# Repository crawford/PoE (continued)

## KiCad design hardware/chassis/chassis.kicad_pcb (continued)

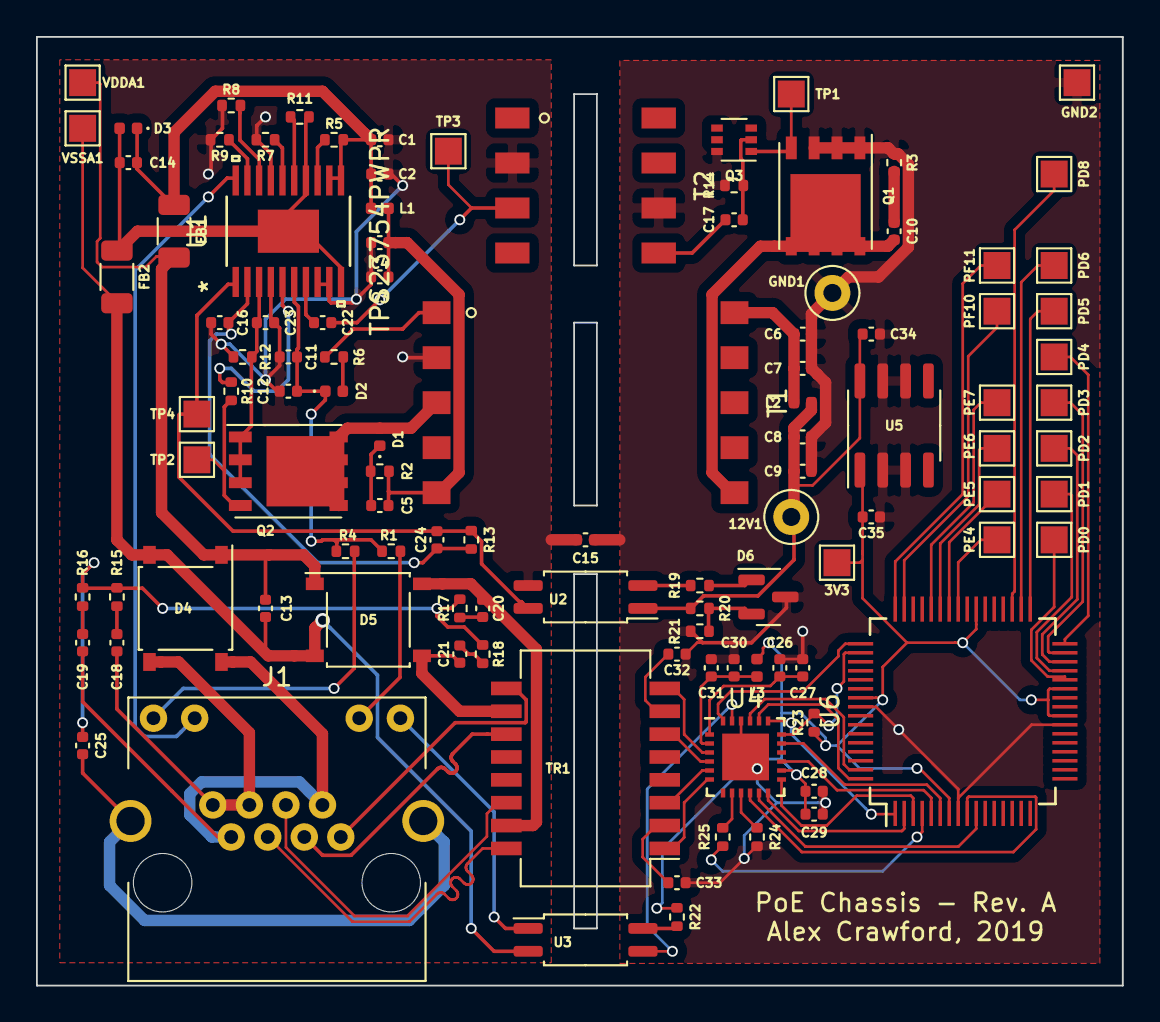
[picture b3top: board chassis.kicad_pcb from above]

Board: 2 copper layers, 60.3 x 52.7 mm, 108 parts (0 on the bottom side), 90 nets.

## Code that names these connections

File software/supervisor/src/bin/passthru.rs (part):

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use led::mono::{self, CommonAnodeLED};
use poe::fault;

type IdentifyLed = CommonAnodeLED<pins::PE4<Output>>;
type NetworkLed = CommonAnodeLED<pins::PE5<Output>>;

#[rtic::app(
    dispatchers = [ CAN0, CAN1, LCD ],
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        gpio_clk.enable();

        // TODO: Move into efm32gg-hal.
        // Configure PE13 as an input with pull-up, and enable interrupts on the falling edge. This
        // is connected to INTRP on the PHY.
        gpio.pe_modeh.modify(|_, w| w.mode13().input());
        gpio.extipselh.modify(|_, w| w.extipsel13().porte());
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        gpio.ien.write(|w| unsafe { w.ext().bits(1 << 13) });

        let gpio = gpio.split(gpio_clk);
        let _swo = gpio.pf2.as_output();

        let mut led_identify = IdentifyLed::new(CommonAnodeLED::new(gpio.pe4.as_opendrain()));
        let mut led_network = NetworkLed::new(CommonAnodeLED::new(gpio.pe5.as_opendrain()));

        led_identify.enable(false);

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            cx.device.ETH,
            &mut delay,
            efm32gg::Pins {
                rmii_rxd0: &mut gpio.pa2.as_input(),
                rmii_refclk: &mut gpio.pa3.as_output(),
                rmii_crsdv: &mut gpio.pa4.as_input(),
                rmii_rxer: &mut gpio.pa5.as_input(),
                rmii_mdio: &mut gpio.pb3.as_output(),
                rmii_mdc: &mut gpio.pb4.as_output(),
                rmii_txd0: &mut gpio.pe15.as_output(),
                rmii_txd1: &mut gpio.pe14.as_output(),
                rmii_txen: &mut gpio.pa0.as_output(),
                rmii_rxd1: &mut gpio.pa1.as_input(),
                phy_reset: &mut gpio.pe11.as_output(),
            },
            KSZ8091::new,
        )
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    let periph = unsafe { efm32gg11b820::Peripherals::steal() };
    let gpio = periph.GPIO.split(periph.CMU.constrain().split().gpio);

    let id = CommonAnodeLED::new(gpio.pe4.as_opendrain());
    let net = CommonAnodeLED::new(gpio.pe5.as_opendrain());

    (id, net)
}
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
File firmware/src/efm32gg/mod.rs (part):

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        // Hold the PHY module in reset
        pins.phy_reset.set_low().ignore();

        // Enable the PHY's reference clock on PA3 (CMU_CLK2 #1)
        cmu.routeloc0.modify(|_, reg| reg.clkout2loc().loc1());
        cmu.routepen.modify(|_, reg| reg.clkout2pen().set_bit());

        // Enable the MDC on PB4 (ETH_MDC #0) and MDIO on PB3 (ETH_MDIO #0)
        eth.routeloc1.write(|reg| {
            reg.rmiiloc().loc0();
            reg.mdioloc().loc0();
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
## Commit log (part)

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2018-03-02 firmware/cargo: update parameters for dev builds
    Development builds will be a bit closer to release builds.
2018-03-02 firmware: initial commit
    This adds an initial LED demo for the EFM32GG11-SLSTK3701A development
    beard.
2018-05-10 cargo: bump efm32gg11b820 to v0.3.0
    This is needed because the SVD was incorrect and didn't allow IFRC to be
    read.
2018-05-31 firmware/ethernet: add initial send/receive logic
    This initial implementation is able to send and receive packets, but
    it's still a little fragile.
2018-05-31 firmware/build: bump rust
    This resuilts in much smaller binaries (12.5% reduction).
2018-07-03 firmware/*: break EFM32GG into a MAC and PHY
    This defines a basic PHY interface so that alternate PHYs may eventually
    be used with the EFM32GG MAC. The KSZ8091 starts to implement this PHY
    interface. The EFM32GG MACPHY also no longer hardcodes the address of
    the PHY. It is dynamically discovered at runtime, further allowing
    alternate PHYs to be used in the future.
2018-07-07 firmware/build: bump rust
    There isn't really any reason for this other than to keep up-to-date.
2018-07-29 firmware/*: apply clippy recommendations
    This also results in smaller code!
2019-01-06 firmware/*: cargo fmt
    rustfmt 1.0.0-stable (4a4e508 2018-11-29)
2019-05-22 firmware/log: adjust logging levels
2019-09-16 hardware/*: remove netlist
    This file is no longer explicitly needed in KiCAD 5.
2019-09-16 hardware/*: various fixes based on review
2019-10-12 firmware/*: fix cortex-m deprecation warning
    cortex-m deprecated NVIC::enable in 0.6.1:
    warning: use of deprecated item 'cortex_m::peripheral::nvic::<impl
    cortex_m::peripheral::NVIC>::enable': Use `NVIC::unmask`
2019-12-08 firmware/main: log panic messages through ITM
    This will no longer light up both LEDs yellow, but instead send the panic message through the ITM.
2020-06-04 stash
2020-12-25 firmware/efm32gg: fix reuse of transmit buffer
    The ethernet module only sets the ownership bit of the first descriptor
    in a frame; not all of the descriptors. I guess I hadn't noticed because
    I've only been transmitting small payloads.
2021-07-05 cargo: update smoltcp
    Updating managed v0.7.2 -> v0.8.0
    Removing smoltcp v0.6.0
    Adding smoltcp v0.8.0 (https://github.com/smoltcp-rs/smoltcp#1134eb28)
2021-07-06 firmware/*: add some more logging
2021-07-11 main: clean up panic and fault handlers
2021-07-11 efm32gg: use slices to create buffer descriptors
    I dunno, this just seems more correct.
2021-07-11 efm32gg: clean up the IRQ
    This uses the LED resources instead of stealing them.
2021-07-11 main: begin migration to rtic
    Most of the functionality has been commented out, but ITM logging does
    work.
2021-07-11 cargo: add ignore-result
2021-07-12 *: pin network buffers
    The DMA buffers and buffer descriptor lists need to be pinned in memory
    since the peripheral is also going to modify those structures.
2021-07-12 cargo: add silent feature
    This disables the logger but does not disable the underlying logging
    mechanism, if it was enabled.
2021-07-21 efm32gg: fix dma import path
    This only worked because of `use crate::efm32gg::dma;` in main.rs.
2022-02-04 cargo: update dependencies, bump smoltcp to v0.8.0
    The latest revision of smoltcp now requires an implementation for a
    random number generator. This patch uses the MCU's TRNG to supply the
    underlying entropy. The network interface's socket set has also been
    absorbed, so there is no need to keep track of it externally.
    Updating crates.io index
    Updating git repository `https://github.com/crawford/efm32gg-hal`
2022-02-11 *: minor cleanups
2022-02-11 efm32gg: use accurate source of delay for PHY power-up
2022-02-11 main: use DHCP instead of static address
2022-02-14 *: use phy interrupts
    Instead of immediately spawning the network handler, wait until the
    link is up. This allows DHCP to complete more quickly because instead
    of incurring the 10-second back-off after transmitting into the void,
    the firmware waits until the PHY is ready to transmit.
    There is a one-second delay between the link-up interrupt and the
    network handler running. I'm not sure why this is needed, but I'll
2022-02-26 *: rework MAC initialization
    This breaks up the initialization into two steps: MDIO and MAC. This
    allows the MDIO to be used to configured the PHY (e.g. reading the
    OUI) before fully configuring the MAC. The MAC address is also now
    returned from the initialization so that it's not hard-coded twice.
2022-07-17 chassis: add library cache
2022-07-24 hardware: prepare for more KiCad projects
2022-07-24 chassis: update footprint for D2 and hide value in schematic
2022-09-06 flyback: use trimpots instead of trimmable resistors
2022-09-06 hardware: fix symbols for gate transistor
    The symbol for Si7898DP had the wrong polarity.
2022-09-06 flyback: add missing diode network across secondary-side gate
2022-09-06 flyback: use internal slope compensation by default
2022-09-06 flyback: associate trimpot footprints
2022-09-06 flyback: use trimpot to make output voltage adjustable
2022-09-06 flyback: remove stray wire
2022-09-06 flyback: add initial board layout
    I think I'm happy with this as-is for the first revision. For the
    future though, I think it might be cleaner to move T2 and C16 to the
    other side of T1. There were also a number of design rule exclusions
    related to the clearance around VSSA and VDDA. I was shooting for a
    spacing of 0.025" as advised by the reference manual, but a few of the
    footprints were too small to accommodate.
2022-09-06 flyback: improve testpoints
    This changes a number of footprints to be through-hole instead of a
    pad. The current sense resistor on the output was also moved to the
    outside of the secondary-side output coupling capacitor; plus, an
    extra testpoint was added to the other side.
2022-09-06 common: add model for primary-side inductor
2022-09-06 flyback: add second earth-coupling capacitor to simplify pcb layout
2022-09-06 flyback: add sheet details
2022-09-16 flyback: update layout with new footprints
    This ended up shuffling quite a bit around. I got rid of the notch in
    the board, since that space is now needed. A lot of this will be
    simplified once the varistors are no longer needed.
2022-10-21 common: add SWD labels to EFM32 symbol
2022-10-21 common: add footprint and model for two-pin terminal block
2022-12-07 passthru: add decoupling cap for internal LDO
    The reference manual also suggests that VREG_VDD should be connected
    to VDD, even though the bypass switch and DC-DC converter are
    disabled. Since that pin is adjacent to DVDD, I'm going to do it
    without looking into why it's recommended.
2022-12-08 passthru: assign the rest of the footprints
    Just going with 0603s for everything except the shut resistor, which I
    already have stocked.
2022-12-11 passthru: fix test point values
2022-12-13 common: add footprint for shielded RJ45 jack
    Splurging for the shielded connector. It'll give a little extra
    strength in case the cable gets yanked.
2022-12-14 passthru: connect Ethernet interrupt
    I know enough of the layout to know that this will work well connected
    anywhere between PE8 and PE13.
2022-12-14 passthru: route the signals for the LEDs
2022-12-15 passthru: use local footprint for PFETs
    This one has 3D models.
2022-12-15 common: add oscillator
2022-12-15 passthru: adjust shape of earth plane
2022-12-16 passthru: increase the resistance of the VDD shunt resistor
    Assuming a maximum VDD current of 600 mA, this will give a maximum
    sense voltage of 0.6 V and 36 mW of power draw.
2022-12-16 passthru: add metadata to schematic and layout
2023-04-21 efm32gg: remove LED configuration
    This was always a bit of a hack to help with debugging. Neither the
    MAC nor PHY should know anything about the LEDs. I tried making this
    more generic with hooks, but it ended up a little unbalanced - the
    LEDs were passed into the interrupt handler, but were stolen by the
    hooks. In the long term, it might make more sense to move all of this
    functionality to RX/TX start/stop hooks.
2023-04-21 efm32gg: remove PHY-enable signal
    Not all boards will be able to shut off power to the PHY like the
    development board can (presumably for testing power consumption).
2023-04-21 efm32gg: reconfigure RMII
    The passthru PCB has a 25 MHz crystal on HFXO, so HFCLK is 25 MHz and
    CLKOUT2 needs to be doubled. The refclk is on PA3, MDIO on PB3, and
    MDC on PB4.
2023-04-26 passthru: add support for identity LED
    Sending a "1" to port 51900 will make the identity LED
    blink. Likewise, sending a "0" will stop it.
2023-04-26 efm32gg: expose link state
2023-04-26 WIP: network: refactor common functionality and add HTTP server
    Split out these into two
2023-05-25 passthru: cleanup silkscreen
    Removed the part designators from the one side of the board, since they
    really aren't necessary, and removed the redundant "+" from the
    caution label.
2023-05-26 rtt: add commands for reading and writing memory
2023-05-26 passthru: fix formatting
2023-06-03 command: fix the interpreter output
    The output should now consistently end in a newline and a new prompt.
2023-06-03 build: bump to Rust 1.70.0
    The preview extensions were removed since they come by default and
    rust-std was removed since it actually refers to the x86_64
    variant (the thumbv7m variant is included by default).
2024-02-19 openocd: reconfigure for dev kit
    I wasn't able to halt the core. The `srst_only` seems to be the
    culprit.
2024-02-19 efm32gg: revert RMII reconfiguration
    This reverts commit 53232dc33c72ce9254cc9bb4cde30802092f9c8c, since
    I'm moving back to the dev kit for now. This really should be moved to
    the board-specific code.
2024-05-12 passthru,slstk3701a: initialize RTT logging earlier
    Since RTT happens entirely in memory, might as well initialize it as
    early as possible.
2025-07-19 Add rust-analyzer to shell
2025-07-22 Refactor interpreter out of RTT terminal
2025-07-22 Fix indentation
2025-07-22 Fix premature socket closure
    I don't fully understand what is happening here. This is old code that
    I haven't investigated in a while. All I know is that without this
    commented out, connections to the socket are immediately closed.
2025-07-22 Allocate more sockets
    No particular reason. I just know that I'll need more and I'm tired of
    hitting panics. This also brings the number of routes in line.
2025-07-22 Add subcommand for printing start of program space
    This is needed in order to actually link binaries destined for that
    address space.
2025-07-22 Remove vestigial logging code
    This hasn't done anything since the logging feature was removed.
2025-07-30 Fix program size calculation
    It's unclear why this was an isize. The length calculation should have
    been in bytes instead of size-of-the-program-space.
2025-07-30 Fix the alignment of the program space
    The size doesn't seem to have increased without the repr(transparent)
    attribute. It was likely overkill anyway.
2025-07-31 Improve the hard fault handler
    This was missing a few flags. I pulled all of this from AN209.
2025-08-11 Bump to Rust 2024 edition
2025-08-11 Get rid of hack in find_handler_by_id
2025-08-14 Add a README for the firmware
2025-09-22 Move apps and supervisor under one workspace
    This should make it easier to share the call API. The gdbinit config
    has been adjusted to address this warning from GDB:
    warning: No executable has been specified and target does not
    support determining executable automatically. Try
    using the "file" command.
2025-09-23 Add an exit command
    This has been helpful for troubleshooting the connection-reuse issue,
    but I imagine it will be useful for scripting (e.g. the test suite).
2025-10-02 Add verbosity flag to apps/call Makefile
2025-10-02 Add supervisor call for testing return values
